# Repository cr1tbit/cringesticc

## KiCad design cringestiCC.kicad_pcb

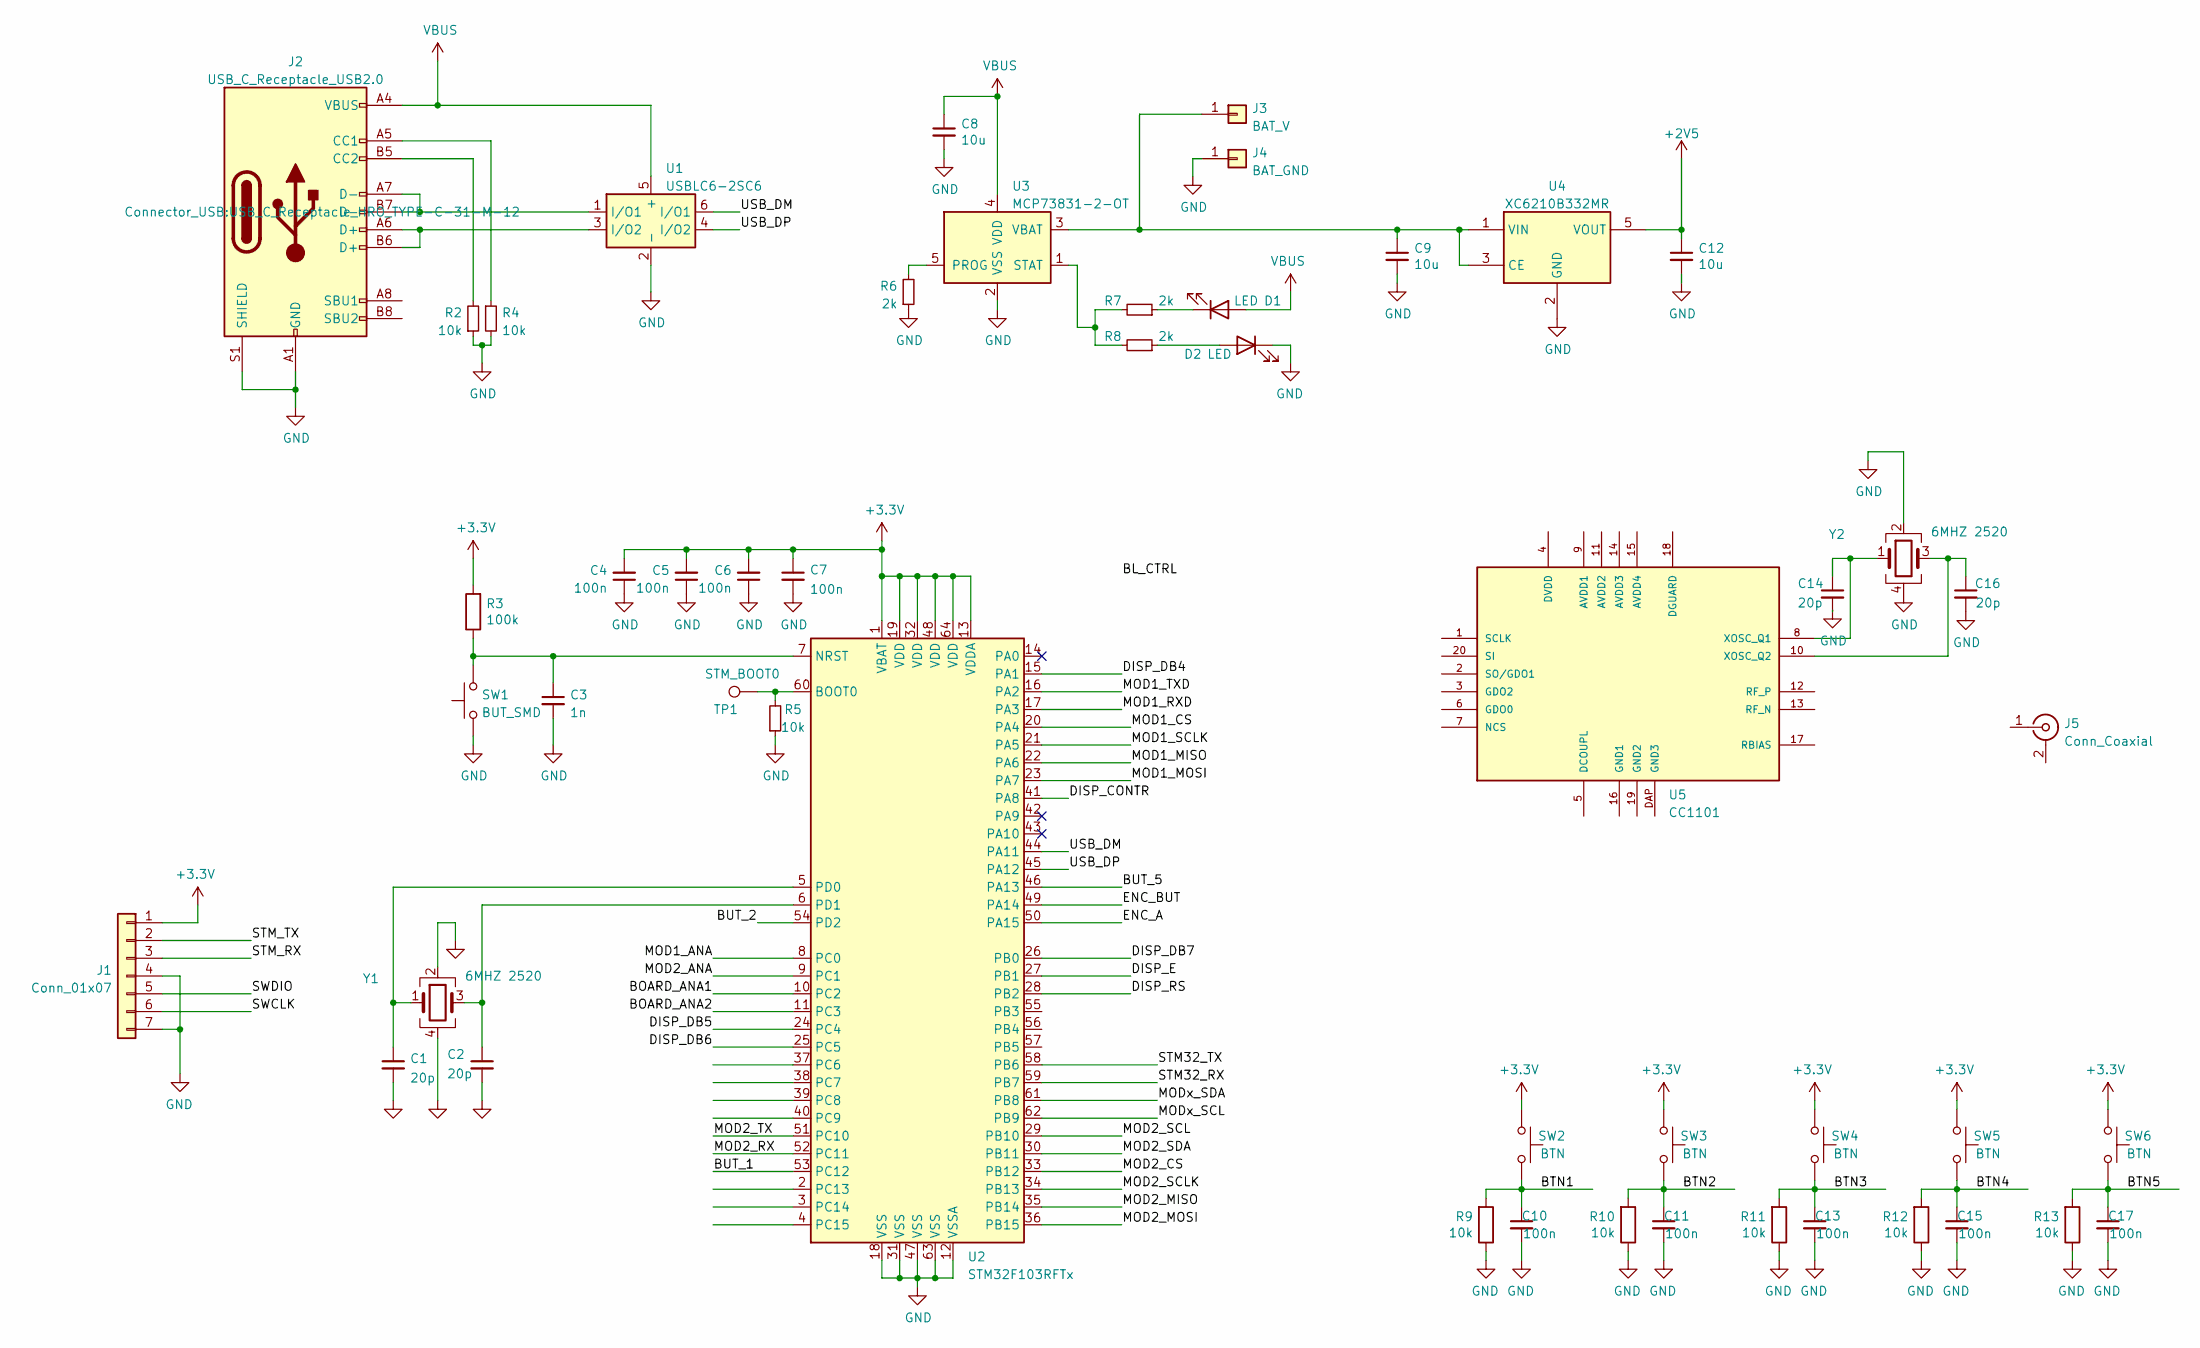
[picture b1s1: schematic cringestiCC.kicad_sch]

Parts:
C1, C2, C14, C16: 20p; C_0402_1005Metric
C3: 1n; C_0402_1005Metric
C4, C5, C6, C7, C10, C11, C13, C15, C17: 100n; C_0402_1005Metric
C8, C9, C12: 10u; C_0402_1005Metric
D1, D2: LED; LED_0603_1608Metric_Pad1.05x0.95mm_HandSolder
J1: Conn_01x07; PinHeader_1x07_P2.54mm_Vertical
J2: USB_C_Receptacle_USB2.0; USB_C_Receptacle_HRO_TYPE-C-31-M-12
J3: BAT_V; TestPoint_Pad_4.0x4.0mm
J4: BAT_GND; TestPoint_Pad_4.0x4.0mm
J5: Conn_Coaxial; SMA_Samtec_SMA-J-P-X-ST-EM1_EdgeMount
R2, R4, R5, R9, R10, R11, R12, R13: 10k; R_0402_1005Metric
R3: 100k; R_0402_1005Metric
R6, R7, R8: 2k; R_0402_1005Metric
SW1: BUT_SMD; Panasonic_EVQPUJ_EVQPUA
SW2, SW3, SW4, SW5, SW6: BTN; Panasonic_EVQPUJ_EVQPUA
TP1: STM_BOOT0; TestPoint_Pad_D1.0mm
U1: USBLC6-2SC6; SOT-23-6
U2: STM32F103RFTx; LQFP-64_10x10mm_P0.5mm
U3: MCP73831-2-OT; SOT-23-5
U4: XC6210B332MR; SOT-23-5
U5: CC1101; Texas_S-PVQFN-N20_EP2.4x2.4mm_ThermalVias
Y1, Y2: 6MHZ 2520; Crystal_SMD_2520-4Pin_2.5x2.0mm

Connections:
+2V5: C12.1, U4.5 (VOUT)
+3V3: C4.2, C5.2, C6.2, C7.1, J1.1, R3.2, SW2.2, SW3.2, SW4.2, SW5.2, SW6.2, U2.1 (VBAT), U2.13 (VDDA), U2.19 (VDD), U2.32 (VDD), U2.48 (VDD), U2.64 (VDD)
/BOARD_ANA1: U2.10 (PC2)
/BOARD_ANA2: U2.11 (PC3)
/BTN1: C10.1, R9.2, SW2.1
/BTN2: C11.1, R10.2, SW3.1
/BTN3: C13.1, R11.2, SW4.1
/BTN4: C15.1, R12.2, SW5.1
/BTN5: C17.1, R13.2, SW6.1
/BUT_1: U2.53 (PC12)
/BUT_2: U2.54 (PD2)
/BUT_5: U2.46 (PA13)
/DISP_CONTR: U2.41 (PA8)
/DISP_DB4: U2.15 (PA1)
/DISP_DB5: U2.24 (PC4)
/DISP_DB6: U2.25 (PC5)
/DISP_DB7: U2.26 (PB0)
/DISP_E: U2.27 (PB1)
/DISP_RS: U2.28 (PB2)
/ENC_A: U2.50 (PA15)
/ENC_BUT: U2.49 (PA14)
/MOD1_ANA: U2.8 (PC0)
/MOD1_CS: U2.20 (PA4)
/MOD1_MISO: U2.22 (PA6)
/MOD1_MOSI: U2.23 (PA7)
/MOD1_RXD: U2.17 (PA3)
/MOD1_SCLK: U2.21 (PA5)
/MOD1_TXD: U2.16 (PA2)
/MOD2_ANA: U2.9 (PC1)
/MOD2_CS: U2.33 (PB12)
/MOD2_MISO: U2.35 (PB14)
/MOD2_MOSI: U2.36 (PB15)
/MOD2_RX: U2.52 (PC11)
/MOD2_SCL: U2.29 (PB10)
/MOD2_SCLK: U2.34 (PB13)
/MOD2_SDA: U2.30 (PB11)
/MOD2_TX: U2.51 (PC10)
/MODx_SCL: U2.62 (PB9)
/MODx_SDA: U2.61 (PB8)
/STM32_RX: U2.59 (PB7)
/STM32_TX: U2.58 (PB6)
/STM_RX: J1.3
/STM_TX: J1.2
/SWCLK: J1.6
/SWDIO: J1.5
/USB_DM: U1.6 (I/O1), U2.44 (PA11)
/USB_DP: U1.4 (I/O2), U2.45 (PA12)
GND: C1.2, C2.2, C3.2, C4.1, C5.1, C6.1, C7.2, C8.2, C9.2, C10.2, C11.2, C12.2, C13.2, C14.2, C15.2, C16.2, C17.2, D2.1 (K), J1.4, J1.7, J2.A1 (GND), J2.A12 (GND), J2.B1 (GND), J2.B12 (GND), J2.S1 (SHIELD), J4.1, R2.1, R4.2, R5.1, R6.1, R9.1, R10.1, R11.1, R12.1, R13.1, SW1.1, U1.2 (-), U2.12 (VSSA), U2.18 (VSS), U2.31 (VSS), U2.47 (VSS), U2.63 (VSS), U3.2 (VSS), U4.2 (GND), Y1.2, Y1.4, Y2.2, Y2.4
unnamed: C1.1, U2.5 (PD0), Y1.1
unnamed: C2.1, U2.6 (PD1), Y1.3
unnamed: C3.1, R3.1, SW1.2, U2.7 (NRST)
unnamed: C9.1, J3.1, U3.3 (VBAT), U4.1 (VIN), U4.3 (CE)
unnamed: C14.1, U5.8 (XOSC_Q1), Y2.1
unnamed: C16.1, U5.10 (XOSC_Q2), Y2.3
unnamed: D1.1 (K), R7.1
unnamed: D2.2 (A), R8.1
unnamed: J2.A5 (CC1), R4.1
unnamed: J2.A6 (D+), J2.B6 (D+), U1.3 (I/O2)
unnamed: J2.A7 (D-), J2.B7 (D-), U1.1 (I/O1)
unnamed: J2.B5 (CC2), R2.2
unnamed: R5.2, TP1.1, U2.60 (BOOT0)
unnamed: R6.2, U3.5 (PROG)
unnamed: R7.2, R8.2, U3.1 (STAT)

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
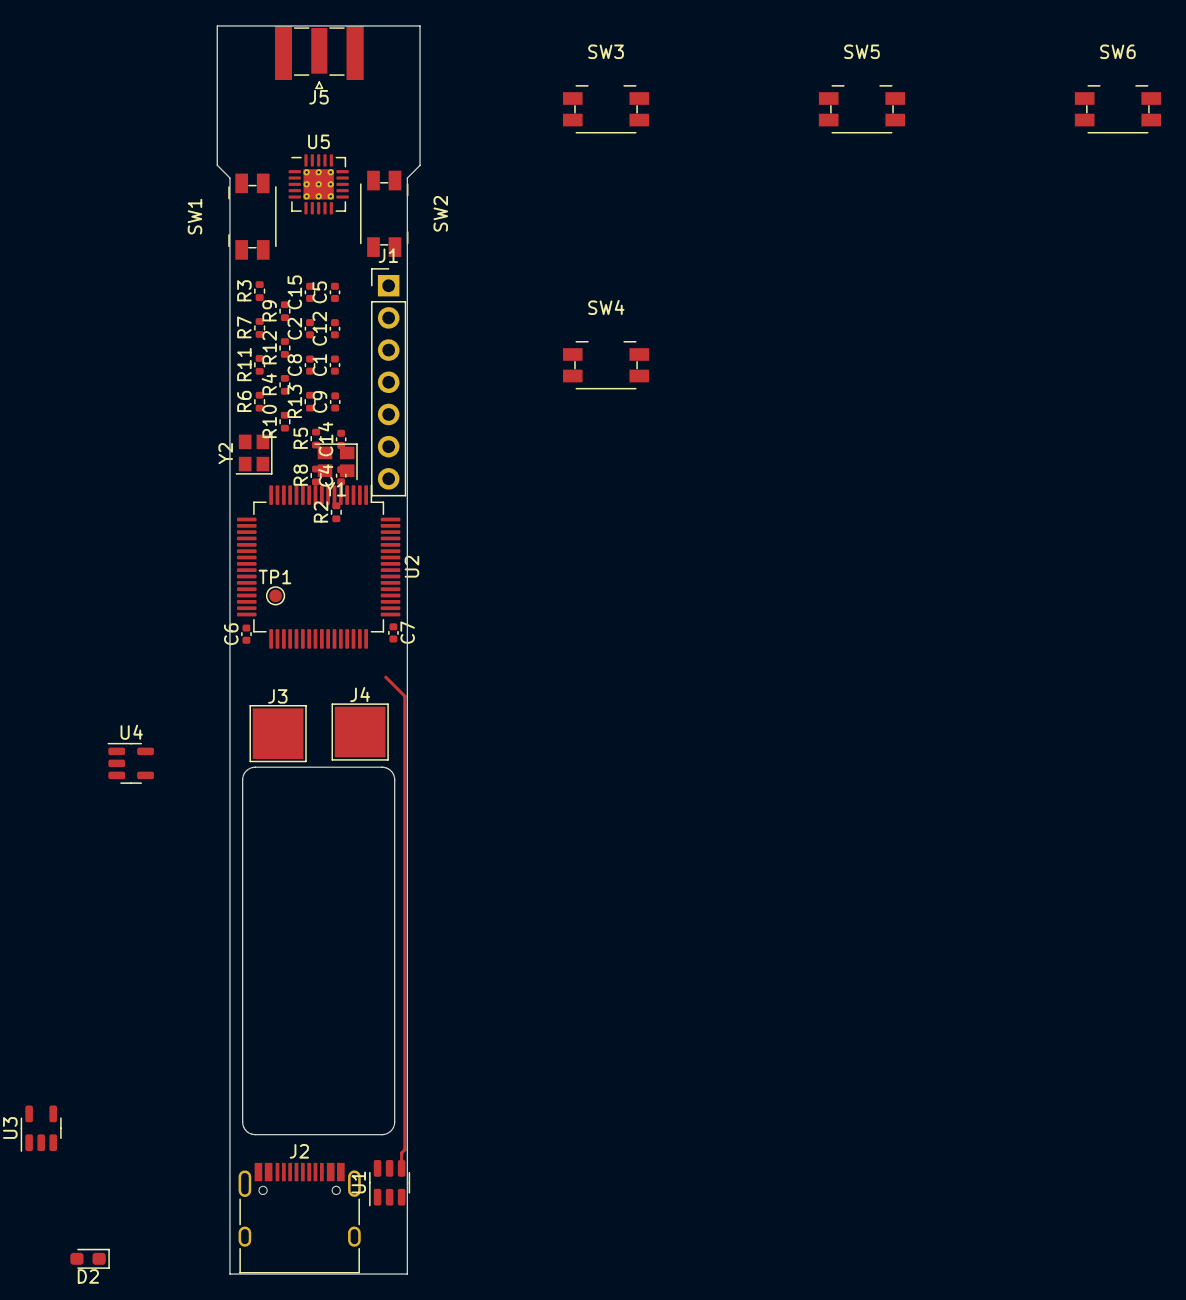
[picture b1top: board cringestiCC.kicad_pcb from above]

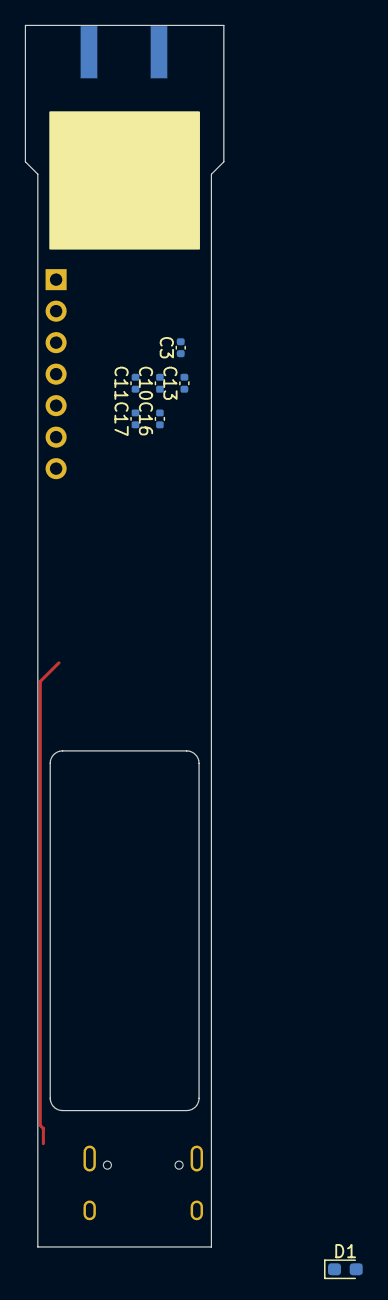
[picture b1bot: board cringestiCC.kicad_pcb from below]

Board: 2 copper layers, 16.0 x 98.5 mm, 50 parts (7 on the bottom side), 27 nets.

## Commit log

2022-09-06 adding hardware
